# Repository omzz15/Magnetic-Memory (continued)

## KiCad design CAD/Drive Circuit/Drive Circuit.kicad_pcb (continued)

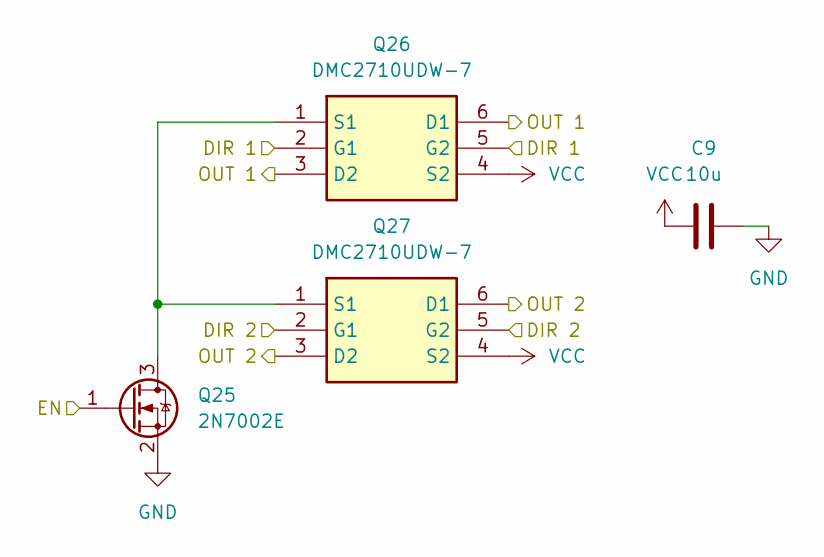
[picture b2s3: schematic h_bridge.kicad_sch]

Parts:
C9: 10u; C_0603_1608Metric_Pad1.08x0.95mm_HandSolder
Q25: 2N7002E; SOT-23
Q26, Q27: DMC2710UDW-7; SOT65P210X110-6N; Mouser Part Number 621-DMC2710UDW-7

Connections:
/Drive Circuit/H Bridge11/EN: Q25.1 (G); also elsewhere on the board
/Drive Circuit/H Bridge/DIR 1: Q26.2 (G1), Q26.5 (G2); also elsewhere on the board
/Drive Circuit/H Bridge/DIR 2: Q27.2 (G1), Q27.5 (G2); also elsewhere on the board
/GRID.A_X10: Q26.3 (D2), Q26.6 (D1); also elsewhere on the board
/GRID.B_X10: Q27.3 (D2), Q27.6 (D1); also elsewhere on the board
GND: C9.1, Q25.2 (S); also elsewhere on the board
unnamed: Q25.3 (D), Q26.1 (S1), Q27.1 (S1)
VCC: C9.2, Q26.4 (S2), Q27.4 (S2); also elsewhere on the board

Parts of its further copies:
C1, C2, C3, C4, C5, C6, C7, C8, C10, C11, C12, C13, C14, C15, C16, C17, C18, C19, C20, C21, C22, C23, C24, C25, C26, C27, C28, C29, C30, C31, C32: 10u; C_0603_1608Metric_Pad1.08x0.95mm_HandSolder
Q1, Q4, Q7, Q10, Q13, Q16, Q19, Q22, Q28, Q31, Q34, Q37, Q40, Q43, Q46, Q49, Q52, Q55, Q58, Q61, Q64, Q67, Q70, Q73, Q76, Q79, Q82, Q85, Q88, Q91, Q94: 2N7002E; SOT-23
Q2, Q3, Q5, Q6, Q8, Q9, Q11, Q12, Q14, Q15, Q17, Q18, Q20, Q21, Q23, Q24, Q29, Q30, Q32, Q33, Q35, Q36, Q38, Q39, Q41, Q42, Q44, Q45, Q47, Q48, Q50, Q51, Q53, Q54, Q56, Q57, Q59, Q60, Q62, Q63, Q65, Q66, Q68, Q69, Q71, Q72, Q74, Q75, Q77, Q78, Q80, Q81, Q83, Q84, Q86, Q87, Q89, Q90, Q92, Q93, Q95, Q96: DMC2710UDW-7; SOT65P210X110-6N; Mouser Part Number 621-DMC2710UDW-7

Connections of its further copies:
/Drive Circuit/H Bridge1/EN: Q40.1 (G); also elsewhere on the board
/Drive Circuit/H Bridge2/EN: Q34.1 (G); also elsewhere on the board
/Drive Circuit/H Bridge3/EN: Q82.1 (G); also elsewhere on the board
/Drive Circuit/H Bridge4/EN: Q85.1 (G); also elsewhere on the board
/Drive Circuit/H Bridge5/EN: Q79.1 (G); also elsewhere on the board
/Drive Circuit/H Bridge6/EN: Q76.1 (G); also elsewhere on the board
/Drive Circuit/H Bridge7/EN: Q73.1 (G); also elsewhere on the board
/Drive Circuit/H Bridge10/EN: Q31.1 (G); also elsewhere on the board
/Drive Circuit/H Bridge12/EN: Q28.1 (G); also elsewhere on the board
/Drive Circuit/H Bridge13/EN: Q70.1 (G); also elsewhere on the board
/Drive Circuit/H Bridge14/EN: Q67.1 (G); also elsewhere on the board
/Drive Circuit/H Bridge15/EN: Q88.1 (G); also elsewhere on the board
/Drive Circuit/H Bridge16/EN: Q91.1 (G); also elsewhere on the board
/Drive Circuit/H Bridge17/EN: Q94.1 (G); also elsewhere on the board
/Drive Circuit/H Bridge18/EN: Q13.1 (G); also elsewhere on the board
/Drive Circuit/H Bridge19/EN: Q16.1 (G); also elsewhere on the board
/Drive Circuit/H Bridge20/EN: Q22.1 (G); also elsewhere on the board
/Drive Circuit/H Bridge21/EN: Q19.1 (G); also elsewhere on the board
/Drive Circuit/H Bridge22/EN: Q46.1 (G); also elsewhere on the board
/Drive Circuit/H Bridge23/EN: Q43.1 (G); also elsewhere on the board
/Drive Circuit/H Bridge24/EN: Q52.1 (G); also elsewhere on the board
/Drive Circuit/H Bridge25/EN: Q49.1 (G); also elsewhere on the board
/Drive Circuit/H Bridge26/EN: Q4.1 (G); also elsewhere on the board
/Drive Circuit/H Bridge27/EN: Q1.1 (G); also elsewhere on the board
/Drive Circuit/H Bridge28/EN: Q7.1 (G); also elsewhere on the board
/Drive Circuit/H Bridge29/EN: Q10.1 (G); also elsewhere on the board
/Drive Circuit/H Bridge30/EN: Q55.1 (G); also elsewhere on the board
/Drive Circuit/H Bridge31/EN: Q61.1 (G); also elsewhere on the board
/Drive Circuit/H Bridge32/EN: Q64.1 (G); also elsewhere on the board
/Drive Circuit/H Bridge33/EN: Q58.1 (G); also elsewhere on the board
/Drive Circuit/H Bridge/DIR 1: Q2.2 (G1), Q2.5 (G2), Q5.2 (G1), Q5.5 (G2), Q8.2 (G1), Q8.5 (G2), Q11.2 (G1), Q11.5 (G2), Q14.2 (G1), Q14.5 (G2), Q17.2 (G1), Q17.5 (G2), Q20.2 (G1), Q20.5 (G2), Q23.2 (G1), Q23.5 (G2), Q29.2 (G1), Q29.5 (G2), Q32.2 (G1), Q32.5 (G2), Q35.2 (G1), Q35.5 (G2), Q38.2 (G1), Q38.5 (G2), Q41.2 (G1), Q41.5 (G2), Q44.2 (G1), Q44.5 (G2), Q47.2 (G1), Q47.5 (G2), Q50.2 (G1), Q50.5 (G2), Q53.2 (G1), Q53.5 (G2), Q56.2 (G1), Q56.5 (G2), Q59.2 (G1), Q59.5 (G2), Q62.2 (G1), Q62.5 (G2), Q65.2 (G1), Q65.5 (G2), Q68.2 (G1), Q68.5 (G2), Q71.2 (G1), Q71.5 (G2), Q74.2 (G1), Q74.5 (G2), Q77.2 (G1), Q77.5 (G2), Q80.2 (G1), Q80.5 (G2), Q83.2 (G1), Q83.5 (G2), Q86.2 (G1), Q86.5 (G2), Q89.2 (G1), Q89.5 (G2), Q92.2 (G1), Q92.5 (G2), Q95.2 (G1), Q95.5 (G2); also elsewhere on the board
/Drive Circuit/H Bridge/DIR 2: Q3.2 (G1), Q3.5 (G2), Q6.2 (G1), Q6.5 (G2), Q9.2 (G1), Q9.5 (G2), Q12.2 (G1), Q12.5 (G2), Q15.2 (G1), Q15.5 (G2), Q18.2 (G1), Q18.5 (G2), Q21.2 (G1), Q21.5 (G2), Q24.2 (G1), Q24.5 (G2), Q30.2 (G1), Q30.5 (G2), Q33.2 (G1), Q33.5 (G2), Q36.2 (G1), Q36.5 (G2), Q39.2 (G1), Q39.5 (G2), Q42.2 (G1), Q42.5 (G2), Q45.2 (G1), Q45.5 (G2), Q48.2 (G1), Q48.5 (G2), Q51.2 (G1), Q51.5 (G2), Q54.2 (G1), Q54.5 (G2), Q57.2 (G1), Q57.5 (G2), Q60.2 (G1), Q60.5 (G2), Q63.2 (G1), Q63.5 (G2), Q66.2 (G1), Q66.5 (G2), Q69.2 (G1), Q69.5 (G2), Q72.2 (G1), Q72.5 (G2), Q75.2 (G1), Q75.5 (G2), Q78.2 (G1), Q78.5 (G2), Q81.2 (G1), Q81.5 (G2), Q84.2 (G1), Q84.5 (G2), Q87.2 (G1), Q87.5 (G2), Q90.2 (G1), Q90.5 (G2), Q93.2 (G1), Q93.5 (G2), Q96.2 (G1), Q96.5 (G2); also elsewhere on the board
/Drive Circuit/H Bridge/EN: Q37.1 (G); also elsewhere on the board
/GRID.A_X1: Q38.3 (D2), Q38.6 (D1); also elsewhere on the board
/GRID.A_X2: Q41.3 (D2), Q41.6 (D1); also elsewhere on the board
/GRID.A_X3: Q35.3 (D2), Q35.6 (D1); also elsewhere on the board
/GRID.A_X4: Q83.3 (D2), Q83.6 (D1); also elsewhere on the board
/GRID.A_X5: Q86.3 (D2), Q86.6 (D1); also elsewhere on the board
/GRID.A_X6: Q80.3 (D2), Q80.6 (D1); also elsewhere on the board
/GRID.A_X7: Q77.3 (D2), Q77.6 (D1); also elsewhere on the board
/GRID.A_X8: Q74.3 (D2), Q74.6 (D1); also elsewhere on the board
/GRID.A_X9: Q32.3 (D2), Q32.6 (D1); also elsewhere on the board
/GRID.A_X11: Q29.3 (D2), Q29.6 (D1); also elsewhere on the board
/GRID.A_X12: Q71.3 (D2), Q71.6 (D1); also elsewhere on the board
/GRID.A_X13: Q68.3 (D2), Q68.6 (D1); also elsewhere on the board
/GRID.A_X14: Q89.3 (D2), Q89.6 (D1); also elsewhere on the board
/GRID.A_X15: Q92.3 (D2), Q92.6 (D1); also elsewhere on the board
/GRID.A_X16: Q95.3 (D2), Q95.6 (D1); also elsewhere on the board
/GRID.A_Y1: Q14.3 (D2), Q14.6 (D1); also elsewhere on the board
/GRID.A_Y2: Q17.3 (D2), Q17.6 (D1); also elsewhere on the board
/GRID.A_Y3: Q23.3 (D2), Q23.6 (D1); also elsewhere on the board
/GRID.A_Y4: Q20.3 (D2), Q20.6 (D1); also elsewhere on the board
/GRID.A_Y5: Q47.3 (D2), Q47.6 (D1); also elsewhere on the board
/GRID.A_Y6: Q44.3 (D2), Q44.6 (D1); also elsewhere on the board
/GRID.A_Y7: Q53.3 (D2), Q53.6 (D1); also elsewhere on the board
/GRID.A_Y8: Q50.3 (D2), Q50.6 (D1); also elsewhere on the board
/GRID.A_Y9: Q5.3 (D2), Q5.6 (D1); also elsewhere on the board
/GRID.A_Y10: Q2.3 (D2), Q2.6 (D1); also elsewhere on the board
/GRID.A_Y11: Q8.3 (D2), Q8.6 (D1); also elsewhere on the board
/GRID.A_Y12: Q11.3 (D2), Q11.6 (D1); also elsewhere on the board
/GRID.A_Y13: Q56.3 (D2), Q56.6 (D1); also elsewhere on the board
/GRID.A_Y14: Q62.3 (D2), Q62.6 (D1); also elsewhere on the board
/GRID.A_Y15: Q65.3 (D2), Q65.6 (D1); also elsewhere on the board
/GRID.A_Y16: Q59.3 (D2), Q59.6 (D1); also elsewhere on the board
/GRID.B_X1: Q39.3 (D2), Q39.6 (D1); also elsewhere on the board
/GRID.B_X2: Q42.3 (D2), Q42.6 (D1); also elsewhere on the board
/GRID.B_X3: Q36.3 (D2), Q36.6 (D1); also elsewhere on the board
/GRID.B_X4: Q84.3 (D2), Q84.6 (D1); also elsewhere on the board
/GRID.B_X5: Q87.3 (D2), Q87.6 (D1); also elsewhere on the board
/GRID.B_X6: Q81.3 (D2), Q81.6 (D1); also elsewhere on the board
/GRID.B_X7: Q78.3 (D2), Q78.6 (D1); also elsewhere on the board
/GRID.B_X8: Q75.3 (D2), Q75.6 (D1); also elsewhere on the board
/GRID.B_X9: Q33.3 (D2), Q33.6 (D1); also elsewhere on the board
/GRID.B_X11: Q30.3 (D2), Q30.6 (D1); also elsewhere on the board
/GRID.B_X12: Q72.3 (D2), Q72.6 (D1); also elsewhere on the board
/GRID.B_X13: Q69.3 (D2), Q69.6 (D1); also elsewhere on the board
/GRID.B_X14: Q90.3 (D2), Q90.6 (D1); also elsewhere on the board
/GRID.B_X15: Q93.3 (D2), Q93.6 (D1); also elsewhere on the board
/GRID.B_X16: Q96.3 (D2), Q96.6 (D1); also elsewhere on the board
/GRID.B_Y1: Q15.3 (D2), Q15.6 (D1); also elsewhere on the board
/GRID.B_Y2: Q18.3 (D2), Q18.6 (D1); also elsewhere on the board
/GRID.B_Y3: Q24.3 (D2), Q24.6 (D1); also elsewhere on the board
/GRID.B_Y4: Q21.3 (D2), Q21.6 (D1); also elsewhere on the board
/GRID.B_Y5: Q48.3 (D2), Q48.6 (D1); also elsewhere on the board
/GRID.B_Y6: Q45.3 (D2), Q45.6 (D1); also elsewhere on the board
/GRID.B_Y7: Q54.3 (D2), Q54.6 (D1); also elsewhere on the board
/GRID.B_Y8: Q51.3 (D2), Q51.6 (D1); also elsewhere on the board
/GRID.B_Y9: Q6.3 (D2), Q6.6 (D1); also elsewhere on the board
/GRID.B_Y10: Q3.3 (D2), Q3.6 (D1); also elsewhere on the board
/GRID.B_Y11: Q9.3 (D2), Q9.6 (D1); also elsewhere on the board
/GRID.B_Y12: Q12.3 (D2), Q12.6 (D1); also elsewhere on the board
/GRID.B_Y13: Q57.3 (D2), Q57.6 (D1); also elsewhere on the board
/GRID.B_Y14: Q63.3 (D2), Q63.6 (D1); also elsewhere on the board
/GRID.B_Y15: Q66.3 (D2), Q66.6 (D1); also elsewhere on the board
/GRID.B_Y16: Q60.3 (D2), Q60.6 (D1); also elsewhere on the board
GND: C1.1, C2.1, C3.1, C4.1, C5.1, C6.1, C7.1, C8.1, C10.1, C11.1, C12.1, C13.1, C14.1, C15.1, C16.1, C17.1, C18.1, C19.1, C20.1, C21.1, C22.1, C23.1, C24.1, C25.1, C26.1, C27.1, C28.1, C29.1, C30.1, C31.1, C32.1, Q1.2 (S), Q4.2 (S), Q7.2 (S), Q10.2 (S), Q13.2 (S), Q16.2 (S), Q19.2 (S), Q22.2 (S), Q28.2 (S), Q31.2 (S), Q34.2 (S), Q37.2 (S), Q40.2 (S), Q43.2 (S), Q46.2 (S), Q49.2 (S), Q52.2 (S), Q55.2 (S), Q58.2 (S), Q61.2 (S), Q64.2 (S), Q67.2 (S), Q70.2 (S), Q73.2 (S), Q76.2 (S), Q79.2 (S), Q82.2 (S), Q85.2 (S), Q88.2 (S), Q91.2 (S), Q94.2 (S); also elsewhere on the board
unnamed: Q1.3 (D), Q2.1 (S1), Q3.1 (S1)
unnamed: Q4.3 (D), Q5.1 (S1), Q6.1 (S1)
unnamed: Q7.3 (D), Q8.1 (S1), Q9.1 (S1)
unnamed: Q10.3 (D), Q11.1 (S1), Q12.1 (S1)
unnamed: Q13.3 (D), Q14.1 (S1), Q15.1 (S1)
unnamed: Q16.3 (D), Q17.1 (S1), Q18.1 (S1)
unnamed: Q19.3 (D), Q20.1 (S1), Q21.1 (S1)
unnamed: Q22.3 (D), Q23.1 (S1), Q24.1 (S1)
unnamed: Q28.3 (D), Q29.1 (S1), Q30.1 (S1)
unnamed: Q31.3 (D), Q32.1 (S1), Q33.1 (S1)
unnamed: Q34.3 (D), Q35.1 (S1), Q36.1 (S1)
unnamed: Q37.3 (D), Q38.1 (S1), Q39.1 (S1)
unnamed: Q40.3 (D), Q41.1 (S1), Q42.1 (S1)
unnamed: Q43.3 (D), Q44.1 (S1), Q45.1 (S1)
unnamed: Q46.3 (D), Q47.1 (S1), Q48.1 (S1)
unnamed: Q49.3 (D), Q50.1 (S1), Q51.1 (S1)
unnamed: Q52.3 (D), Q53.1 (S1), Q54.1 (S1)
unnamed: Q55.3 (D), Q56.1 (S1), Q57.1 (S1)
unnamed: Q58.3 (D), Q59.1 (S1), Q60.1 (S1)
unnamed: Q61.3 (D), Q62.1 (S1), Q63.1 (S1)
unnamed: Q64.3 (D), Q65.1 (S1), Q66.1 (S1)
unnamed: Q67.3 (D), Q68.1 (S1), Q69.1 (S1)
unnamed: Q70.3 (D), Q71.1 (S1), Q72.1 (S1)
unnamed: Q73.3 (D), Q74.1 (S1), Q75.1 (S1)
unnamed: Q76.3 (D), Q77.1 (S1), Q78.1 (S1)
unnamed: Q79.3 (D), Q80.1 (S1), Q81.1 (S1)
unnamed: Q82.3 (D), Q83.1 (S1), Q84.1 (S1)
unnamed: Q85.3 (D), Q86.1 (S1), Q87.1 (S1)
unnamed: Q88.3 (D), Q89.1 (S1), Q90.1 (S1)
unnamed: Q91.3 (D), Q92.1 (S1), Q93.1 (S1)
unnamed: Q94.3 (D), Q95.1 (S1), Q96.1 (S1)
VCC: C1.2, C2.2, C3.2, C4.2, C5.2, C6.2, C7.2, C8.2, C10.2, C11.2, C12.2, C13.2, C14.2, C15.2, C16.2, C17.2, C18.2, C19.2, C20.2, C21.2, C22.2, C23.2, C24.2, C25.2, C26.2, C27.2, C28.2, C29.2, C30.2, C31.2, C32.2, Q2.4 (S2), Q3.4 (S2), Q5.4 (S2), Q6.4 (S2), Q8.4 (S2), Q9.4 (S2), Q11.4 (S2), Q12.4 (S2), Q14.4 (S2), Q15.4 (S2), Q17.4 (S2), Q18.4 (S2), Q20.4 (S2), Q21.4 (S2), Q23.4 (S2), Q24.4 (S2), Q29.4 (S2), Q30.4 (S2), Q32.4 (S2), Q33.4 (S2), Q35.4 (S2), Q36.4 (S2), Q38.4 (S2), Q39.4 (S2), Q41.4 (S2), Q42.4 (S2), Q44.4 (S2), Q45.4 (S2), Q47.4 (S2), Q48.4 (S2), Q50.4 (S2), Q51.4 (S2), Q53.4 (S2), Q54.4 (S2), Q56.4 (S2), Q57.4 (S2), Q59.4 (S2), Q60.4 (S2), Q62.4 (S2), Q63.4 (S2), Q65.4 (S2), Q66.4 (S2), Q68.4 (S2), Q69.4 (S2), Q71.4 (S2), Q72.4 (S2), Q74.4 (S2), Q75.4 (S2), Q77.4 (S2), Q78.4 (S2), Q80.4 (S2), Q81.4 (S2), Q83.4 (S2), Q84.4 (S2), Q86.4 (S2), Q87.4 (S2), Q89.4 (S2), Q90.4 (S2), Q92.4 (S2), Q93.4 (S2), Q95.4 (S2), Q96.4 (S2); also elsewhere on the board

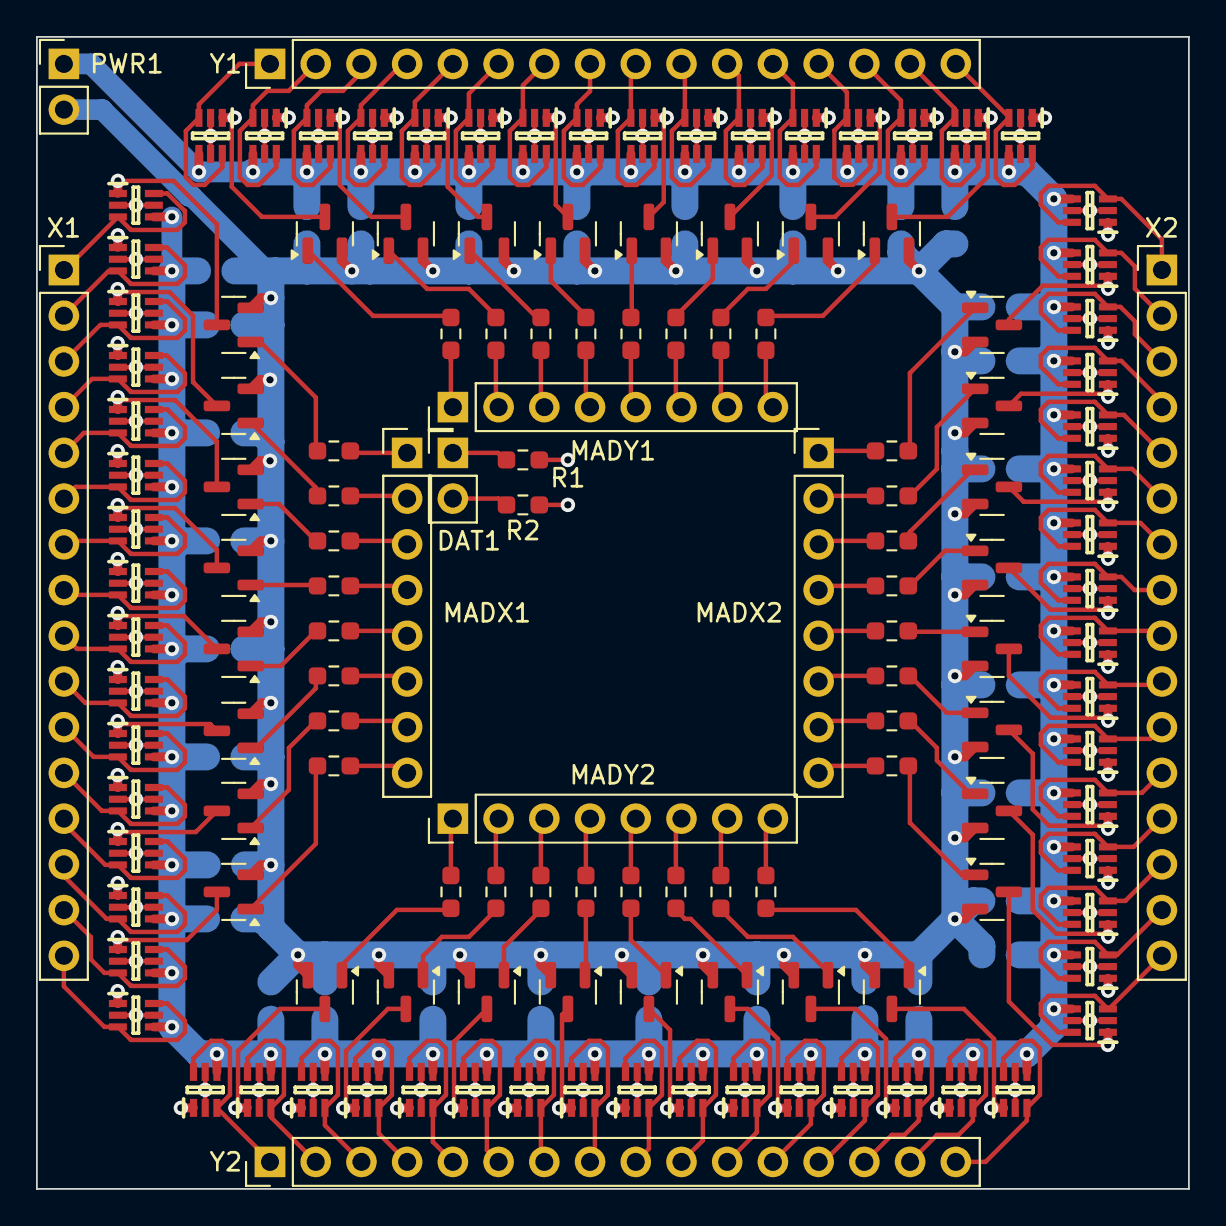
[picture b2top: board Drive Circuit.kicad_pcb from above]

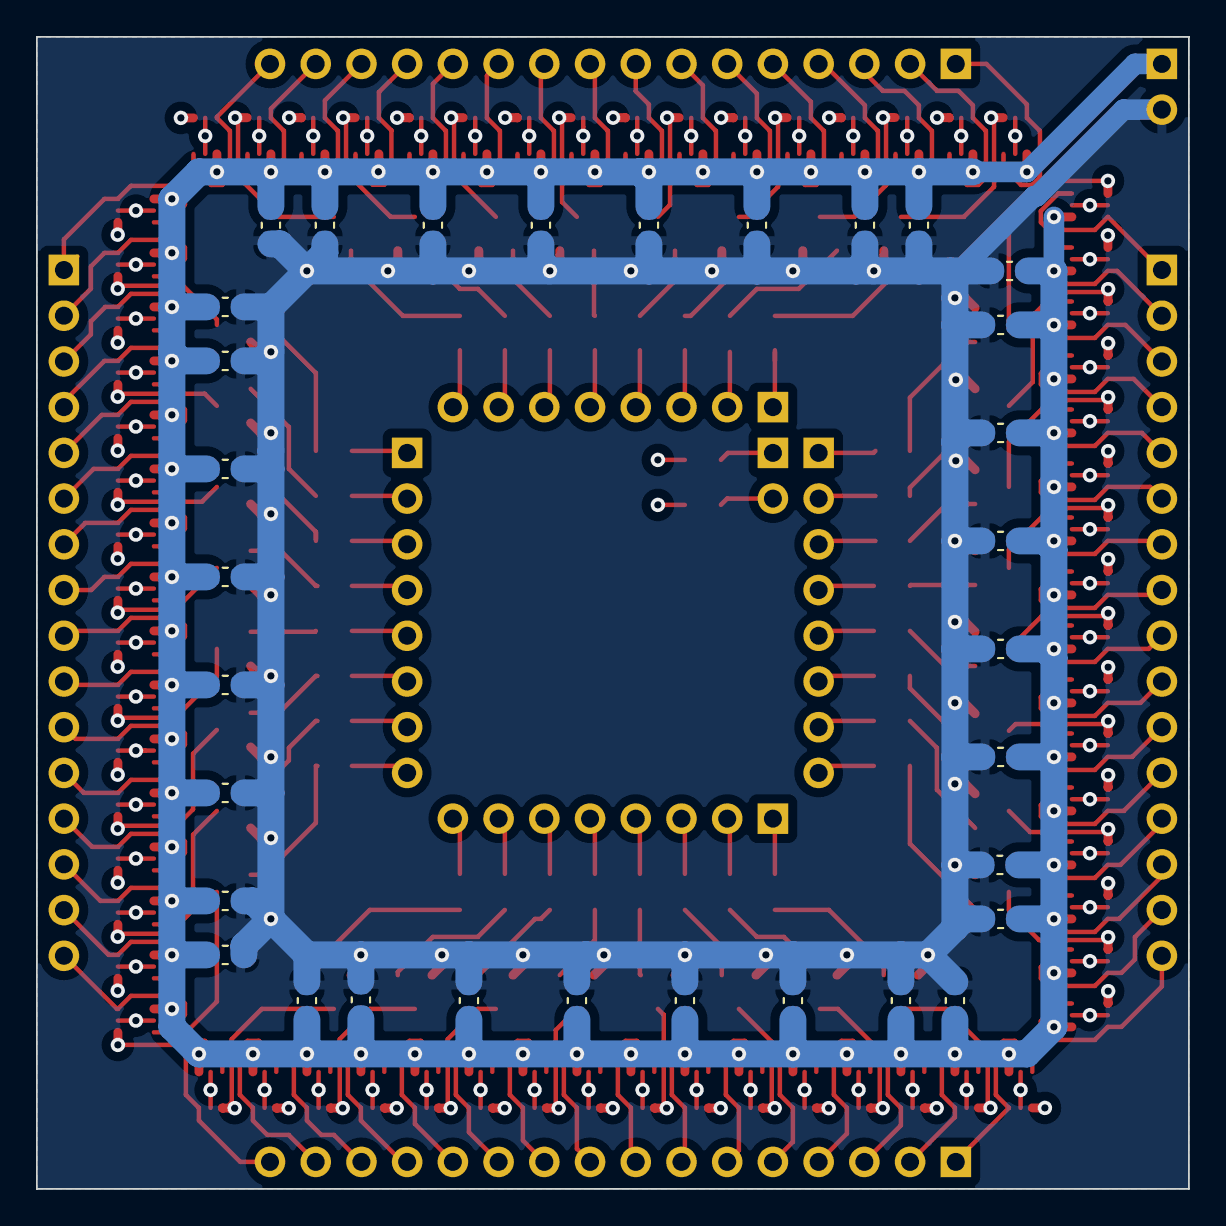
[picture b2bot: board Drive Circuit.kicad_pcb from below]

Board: 4 copper layers, 64.0 x 64.0 mm, 172 parts (32 on the bottom side), 166 nets.

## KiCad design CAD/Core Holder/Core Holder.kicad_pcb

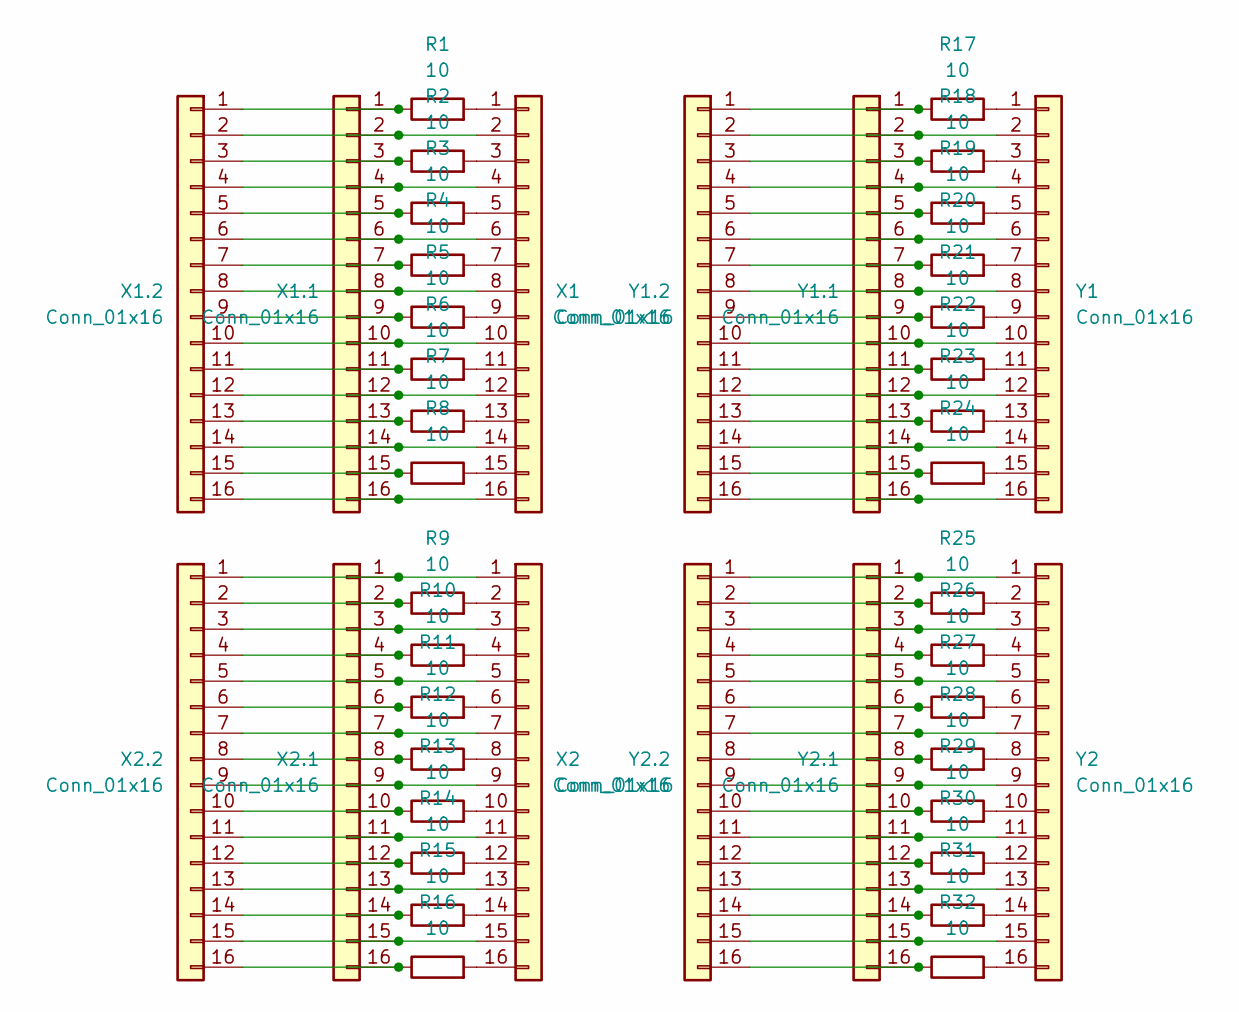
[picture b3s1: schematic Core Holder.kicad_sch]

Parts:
R1, R2, R3, R4, R5, R6, R7, R8, R9, R10, R11, R12, R13, R14, R15, R16, R17, R18, R19, R20, R21, R22, R23, R24, R25, R26, R27, R28, R29, R30, R31, R32: 10; R_0603_1608Metric_Pad0.98x0.95mm_HandSolder
X1, X1.1, X1.2, X2, X2.1, X2.2: Conn_01x16; PinHeader_1x16_P2.54mm_Vertical
Y1, Y1.1, Y1.2, Y2, Y2.1, Y2.2: Conn_01x16; PinHeader_1x16_P2.54mm_Vertical

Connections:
unnamed: R1.2, X1.1
unnamed: X1.2, X1.1.2, X1.2.2
unnamed: R2.2, X1.3
unnamed: X1.4, X1.1.4, X1.2.4
unnamed: R3.2, X1.5
unnamed: X1.6, X1.1.6, X1.2.6
unnamed: R4.2, X1.7
unnamed: X1.8, X1.1.8, X1.2.8
unnamed: R5.2, X1.9
unnamed: X1.10, X1.1.10, X1.2.10
unnamed: R6.2, X1.11
unnamed: X1.12, X1.1.12, X1.2.12
unnamed: R7.2, X1.13
unnamed: X1.14, X1.1.14, X1.2.14
unnamed: R8.2, X1.15
unnamed: X1.16, X1.1.16, X1.2.16
unnamed: R1.1, X1.1.1, X1.2.1
unnamed: R2.1, X1.1.3, X1.2.3
unnamed: R3.1, X1.1.5, X1.2.5
unnamed: R4.1, X1.1.7, X1.2.7
unnamed: R5.1, X1.1.9, X1.2.9
unnamed: R6.1, X1.1.11, X1.2.11
unnamed: R7.1, X1.1.13, X1.2.13
unnamed: R8.1, X1.1.15, X1.2.15
unnamed: X2.1, X2.1.1, X2.2.1
unnamed: R9.2, X2.2
unnamed: X2.3, X2.1.3, X2.2.3
unnamed: R10.2, X2.4
unnamed: X2.5, X2.1.5, X2.2.5
unnamed: R11.2, X2.6
unnamed: X2.7, X2.1.7, X2.2.7
unnamed: R12.2, X2.8
unnamed: X2.9, X2.1.9, X2.2.9
unnamed: R13.2, X2.10
unnamed: X2.11, X2.1.11, X2.2.11
unnamed: R14.2, X2.12
unnamed: X2.13, X2.1.13, X2.2.13
unnamed: R15.2, X2.14
unnamed: X2.15, X2.1.15, X2.2.15
unnamed: R16.2, X2.16
unnamed: R9.1, X2.1.2, X2.2.2
unnamed: R10.1, X2.1.4, X2.2.4
unnamed: R11.1, X2.1.6, X2.2.6
unnamed: R12.1, X2.1.8, X2.2.8
unnamed: R13.1, X2.1.10, X2.2.10
unnamed: R14.1, X2.1.12, X2.2.12
unnamed: R15.1, X2.1.14, X2.2.14
unnamed: R16.1, X2.1.16, X2.2.16
unnamed: R17.2, Y1.1
unnamed: Y1.2, Y1.1.2, Y1.2.2
unnamed: R18.2, Y1.3
unnamed: Y1.4, Y1.1.4, Y1.2.4
unnamed: R19.2, Y1.5
unnamed: Y1.6, Y1.1.6, Y1.2.6
unnamed: R20.2, Y1.7
unnamed: Y1.8, Y1.1.8, Y1.2.8
unnamed: R21.2, Y1.9
unnamed: Y1.10, Y1.1.10, Y1.2.10
unnamed: R22.2, Y1.11
unnamed: Y1.12, Y1.1.12, Y1.2.12
unnamed: R23.2, Y1.13
unnamed: Y1.14, Y1.1.14, Y1.2.14
unnamed: R24.2, Y1.15
unnamed: Y1.16, Y1.1.16, Y1.2.16
unnamed: R17.1, Y1.1.1, Y1.2.1
unnamed: R18.1, Y1.1.3, Y1.2.3
unnamed: R19.1, Y1.1.5, Y1.2.5
unnamed: R20.1, Y1.1.7, Y1.2.7
unnamed: R21.1, Y1.1.9, Y1.2.9
unnamed: R22.1, Y1.1.11, Y1.2.11
unnamed: R23.1, Y1.1.13, Y1.2.13
unnamed: R24.1, Y1.1.15, Y1.2.15
unnamed: Y2.1, Y2.1.1, Y2.2.1
unnamed: R25.2, Y2.2
unnamed: Y2.3, Y2.1.3, Y2.2.3
unnamed: R26.2, Y2.4
unnamed: Y2.5, Y2.1.5, Y2.2.5
unnamed: R27.2, Y2.6
unnamed: Y2.7, Y2.1.7, Y2.2.7
unnamed: R28.2, Y2.8
unnamed: Y2.9, Y2.1.9, Y2.2.9
unnamed: R29.2, Y2.10
unnamed: Y2.11, Y2.1.11, Y2.2.11
unnamed: R30.2, Y2.12
unnamed: Y2.13, Y2.1.13, Y2.2.13
unnamed: R31.2, Y2.14
unnamed: Y2.15, Y2.1.15, Y2.2.15
unnamed: R32.2, Y2.16
unnamed: R25.1, Y2.1.2, Y2.2.2
unnamed: R26.1, Y2.1.4, Y2.2.4
unnamed: R27.1, Y2.1.6, Y2.2.6
unnamed: R28.1, Y2.1.8, Y2.2.8
unnamed: R29.1, Y2.1.10, Y2.2.10
unnamed: R30.1, Y2.1.12, Y2.2.12
unnamed: R31.1, Y2.1.14, Y2.2.14
unnamed: R32.1, Y2.1.16, Y2.2.16

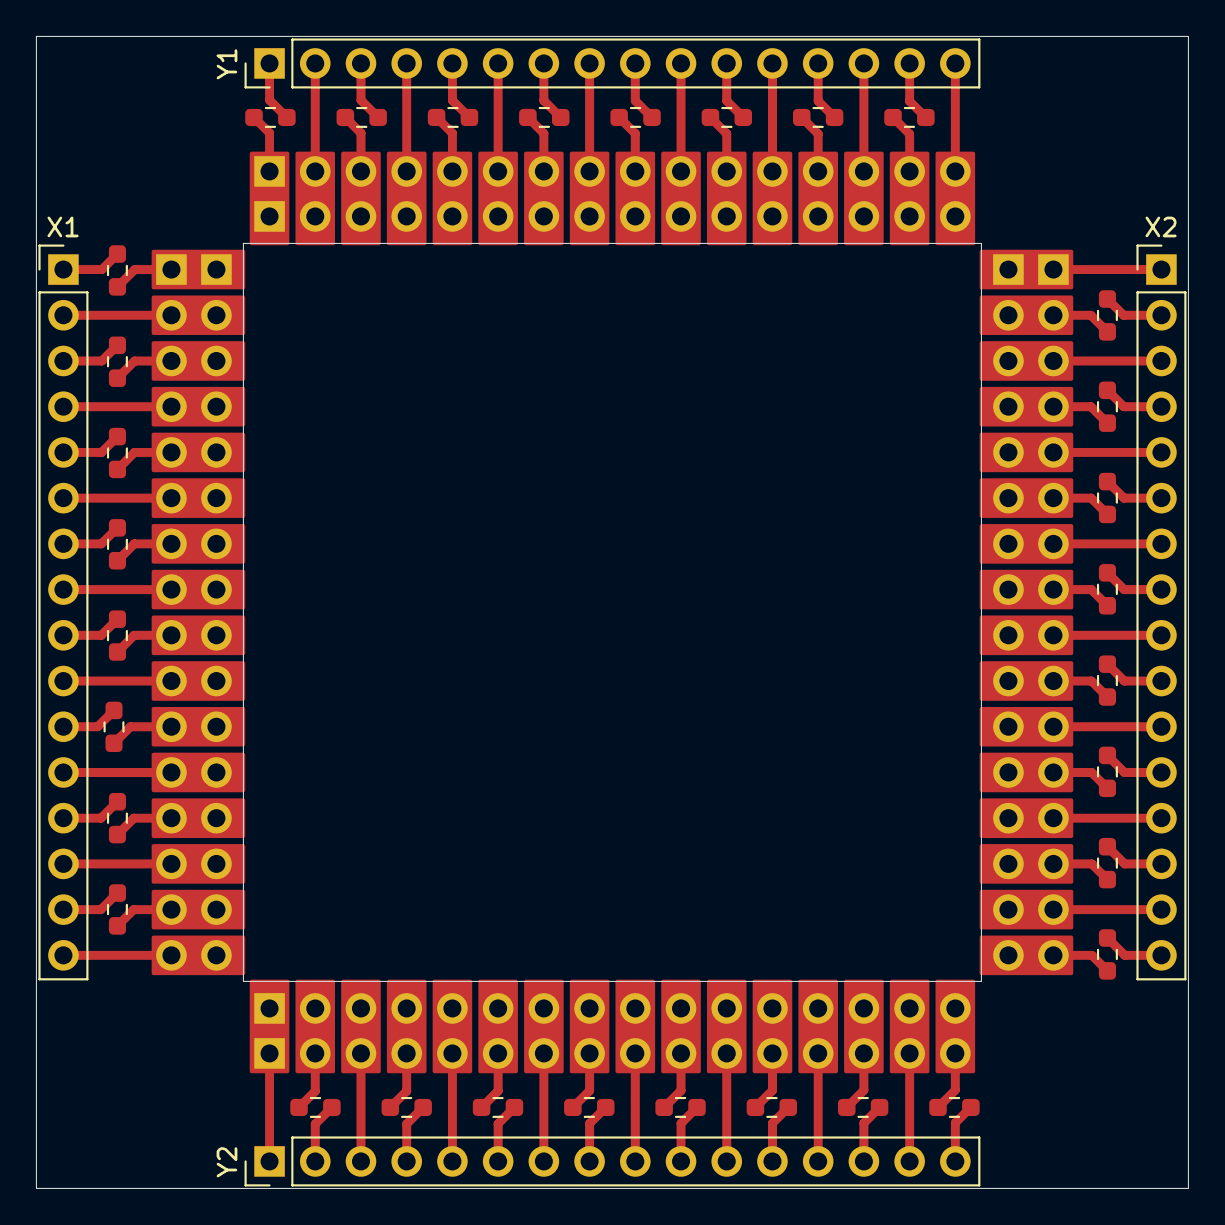
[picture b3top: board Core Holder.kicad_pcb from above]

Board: 2 copper layers, 64.0 x 64.0 mm, 44 parts (0 on the bottom side), 96 nets.

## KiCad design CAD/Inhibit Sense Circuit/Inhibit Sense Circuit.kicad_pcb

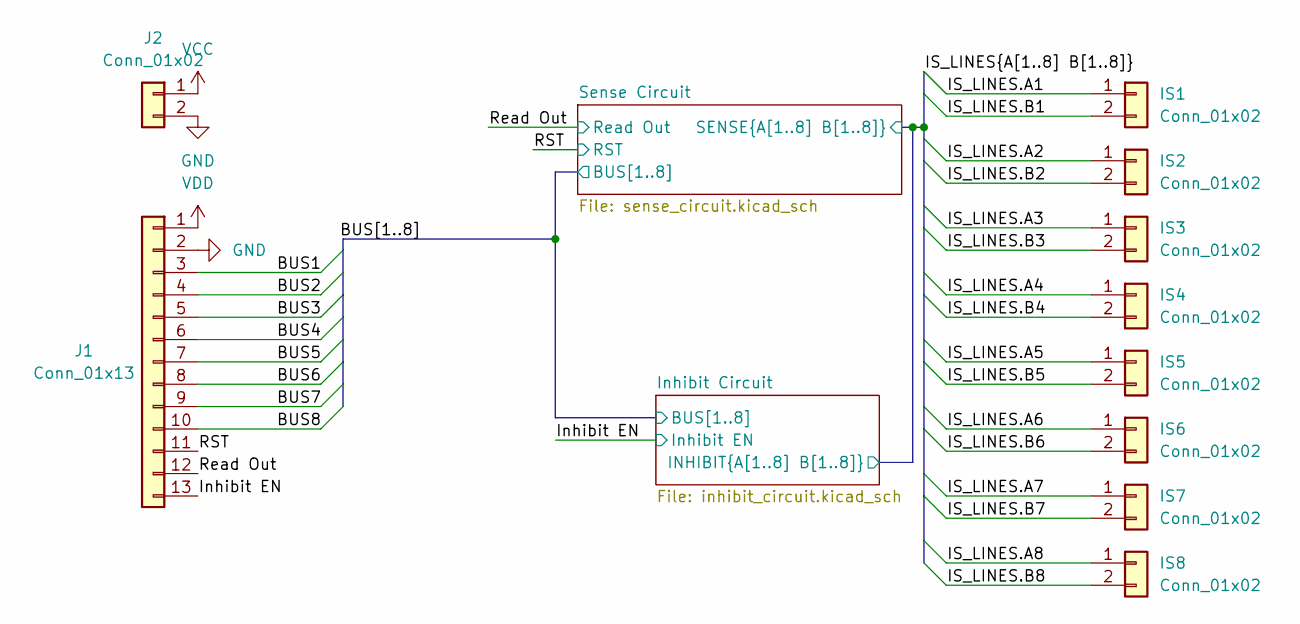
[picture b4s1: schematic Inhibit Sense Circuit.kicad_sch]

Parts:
IS1, IS2, IS3, IS4, IS5, IS6, IS7, IS8: Conn_01x02; PinHeader_1x02_P2.54mm_Vertical
J1: Conn_01x13; PinHeader_1x13_P2.54mm_Vertical
J2: Conn_01x02; PinHeader_1x02_P2.54mm_Vertical

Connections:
/BUS1: J1.3; also elsewhere on the board
/BUS2: J1.4; also elsewhere on the board
/BUS3: J1.5; also elsewhere on the board
/BUS4: J1.6; also elsewhere on the board
/BUS5: J1.7; also elsewhere on the board
/BUS6: J1.8; also elsewhere on the board
/BUS7: J1.9; also elsewhere on the board
/BUS8: J1.10; also elsewhere on the board
/IS_LINES.A1: IS1.1; also elsewhere on the board
/IS_LINES.A2: IS2.1; also elsewhere on the board
/IS_LINES.A3: IS3.1; also elsewhere on the board
/IS_LINES.A4: IS4.1; also elsewhere on the board
/IS_LINES.A5: IS5.1; also elsewhere on the board
/IS_LINES.A6: IS6.1; also elsewhere on the board
/IS_LINES.A7: IS7.1; also elsewhere on the board
/IS_LINES.A8: IS8.1; also elsewhere on the board
/IS_LINES.B1: IS1.2; also elsewhere on the board
/IS_LINES.B2: IS2.2; also elsewhere on the board
/IS_LINES.B3: IS3.2; also elsewhere on the board
/IS_LINES.B4: IS4.2; also elsewhere on the board
/IS_LINES.B5: IS5.2; also elsewhere on the board
/IS_LINES.B6: IS6.2; also elsewhere on the board
/IS_LINES.B7: IS7.2; also elsewhere on the board
/IS_LINES.B8: IS8.2; also elsewhere on the board
/Inhibit EN: J1.13; also elsewhere on the board
/RST: J1.11; also elsewhere on the board
/Read Out: J1.12; also elsewhere on the board
GND: J1.2, J2.2; also elsewhere on the board
VCC: J2.1; also elsewhere on the board
VDD: J1.1; also elsewhere on the board

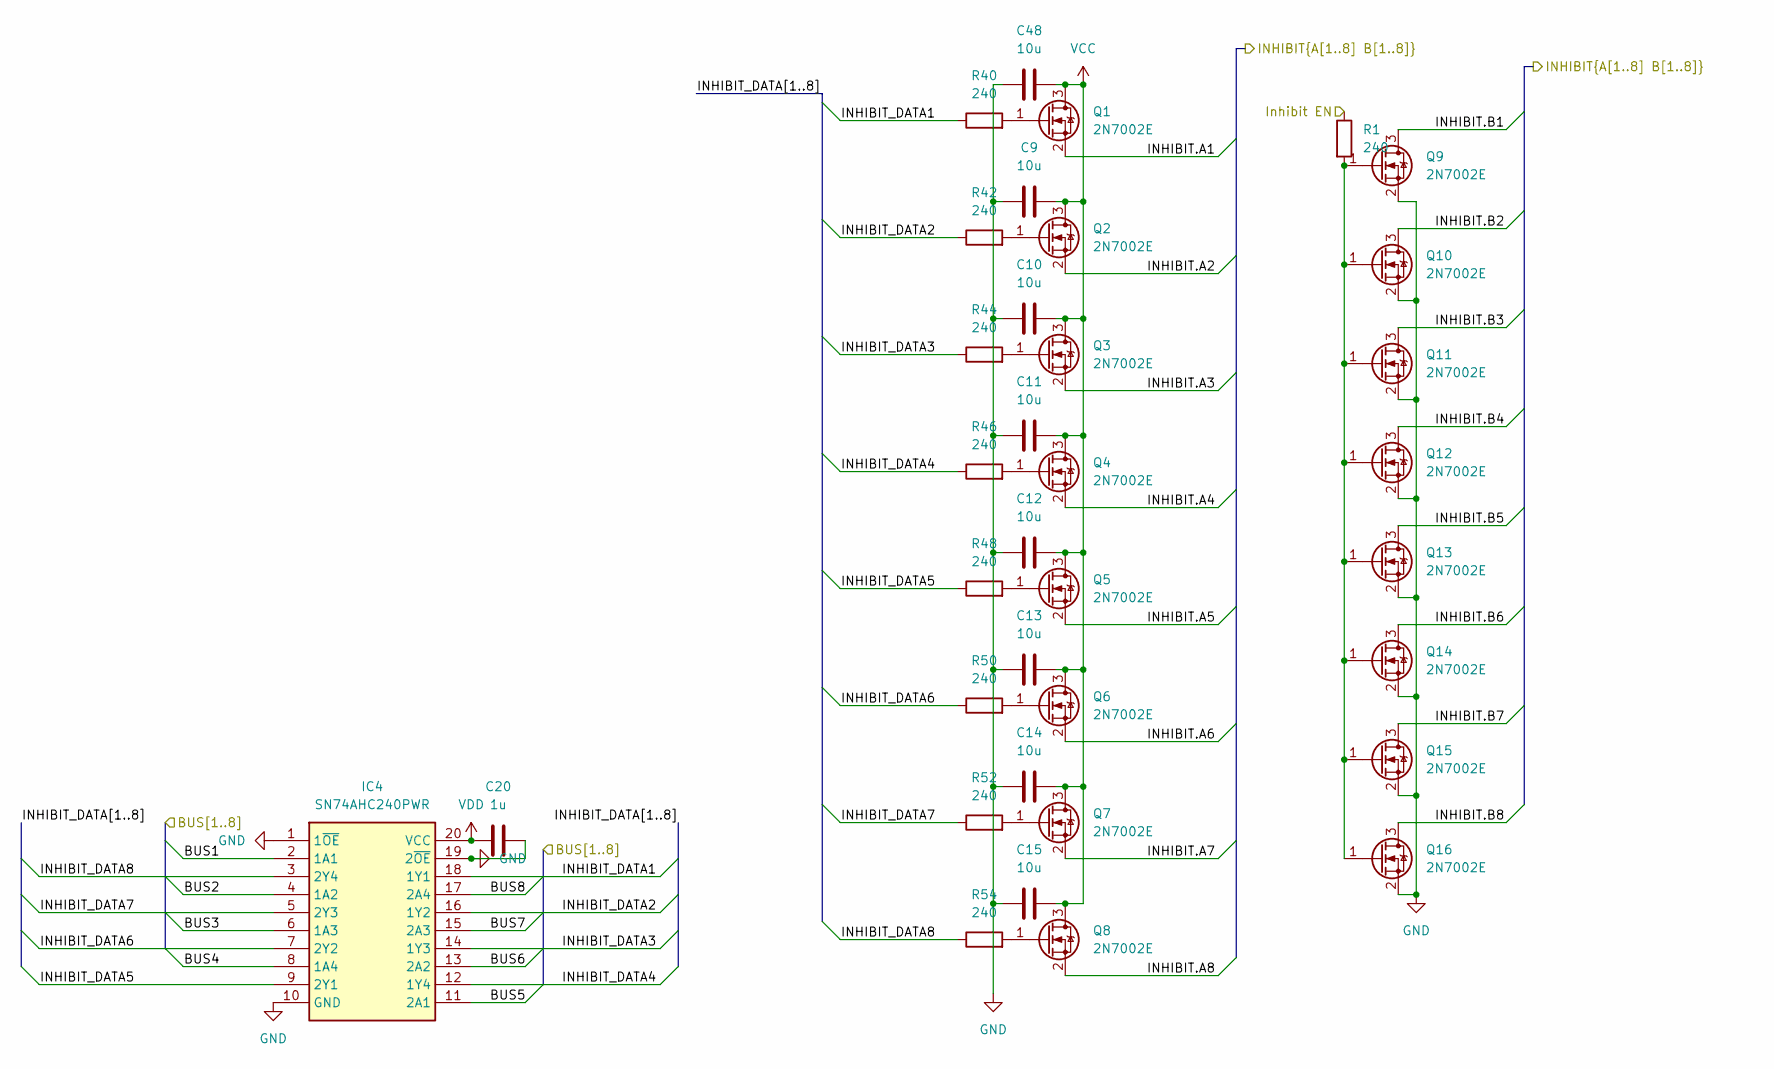
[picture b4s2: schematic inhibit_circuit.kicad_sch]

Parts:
C9, C10, C11, C12, C13, C14, C15, C48: 10u; C_0603_1608Metric_Pad1.08x0.95mm_HandSolder
C20: 1u; C_0603_1608Metric_Pad1.08x0.95mm_HandSolder
IC4: SN74AHC240PWR; SOP65P640X120-20N; Mouser Part Number 595-SN74AHC240PWR
Q1, Q2, Q3, Q4, Q5, Q6, Q7, Q8, Q9, Q10, Q11, Q12, Q13, Q14, Q15, Q16: 2N7002E; SOT-23
R1, R40, R42, R44, R46, R48, R50, R52, R54: 240; R_0603_1608Metric_Pad0.98x0.95mm_HandSolder

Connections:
/BUS1: IC4.2 (1A1); also elsewhere on the board
/BUS2: IC4.4 (1A2); also elsewhere on the board
/BUS3: IC4.6 (1A3); also elsewhere on the board
/BUS4: IC4.8 (1A4); also elsewhere on the board
/BUS5: IC4.11 (2A1); also elsewhere on the board
/BUS6: IC4.13 (2A2); also elsewhere on the board
/BUS7: IC4.15 (2A3); also elsewhere on the board
/BUS8: IC4.17 (2A4); also elsewhere on the board
/IS_LINES.A1: Q1.2 (S); also elsewhere on the board
/IS_LINES.A2: Q2.2 (S); also elsewhere on the board
/IS_LINES.A3: Q3.2 (S); also elsewhere on the board
/IS_LINES.A4: Q4.2 (S); also elsewhere on the board
/IS_LINES.A5: Q5.2 (S); also elsewhere on the board
/IS_LINES.A6: Q6.2 (S); also elsewhere on the board
/IS_LINES.A7: Q7.2 (S); also elsewhere on the board
/IS_LINES.A8: Q8.2 (S); also elsewhere on the board
/IS_LINES.B1: Q9.3 (D); also elsewhere on the board
/IS_LINES.B2: Q10.3 (D); also elsewhere on the board
/IS_LINES.B3: Q11.3 (D); also elsewhere on the board
/IS_LINES.B4: Q12.3 (D); also elsewhere on the board
/IS_LINES.B5: Q13.3 (D); also elsewhere on the board
/IS_LINES.B6: Q14.3 (D); also elsewhere on the board
/IS_LINES.B7: Q15.3 (D); also elsewhere on the board
/IS_LINES.B8: Q16.3 (D); also elsewhere on the board
/Inhibit Circuit/INHIBIT_DATA1: IC4.18 (1Y1), R40.1
/Inhibit Circuit/INHIBIT_DATA2: IC4.16 (1Y2), R42.1
/Inhibit Circuit/INHIBIT_DATA3: IC4.14 (1Y3), R44.1
/Inhibit Circuit/INHIBIT_DATA4: IC4.12 (1Y4), R46.1
/Inhibit Circuit/INHIBIT_DATA5: IC4.9 (2Y1), R48.1
/Inhibit Circuit/INHIBIT_DATA6: IC4.7 (2Y2), R50.1
/Inhibit Circuit/INHIBIT_DATA7: IC4.5 (2Y3), R52.1
/Inhibit Circuit/INHIBIT_DATA8: IC4.3 (2Y4), R54.1
/Inhibit EN: R1.1; also elsewhere on the board
GND: C9.1, C10.1, C11.1, C12.1, C13.1, C14.1, C15.1, C20.2, C48.1, IC4.1 (1~OE), IC4.10 (GND), IC4.19 (2~OE), Q9.2 (S), Q10.2 (S), Q11.2 (S), Q12.2 (S), Q13.2 (S), Q14.2 (S), Q15.2 (S), Q16.2 (S); also elsewhere on the board
unnamed: Q1.1 (G), R40.2
unnamed: Q2.1 (G), R42.2
unnamed: Q3.1 (G), R44.2
unnamed: Q4.1 (G), R46.2
unnamed: Q5.1 (G), R48.2
unnamed: Q6.1 (G), R50.2
unnamed: Q7.1 (G), R52.2
unnamed: Q8.1 (G), R54.2
unnamed: Q9.1 (G), Q10.1 (G), Q11.1 (G), Q12.1 (G), Q13.1 (G), Q14.1 (G), Q15.1 (G), Q16.1 (G), R1.2
VCC: C9.2, C10.2, C11.2, C12.2, C13.2, C14.2, C15.2, C48.2, Q1.3 (D), Q2.3 (D), Q3.3 (D), Q4.3 (D), Q5.3 (D), Q6.3 (D), Q7.3 (D), Q8.3 (D); also elsewhere on the board
VDD: C20.1, IC4.20 (VCC); also elsewhere on the board
